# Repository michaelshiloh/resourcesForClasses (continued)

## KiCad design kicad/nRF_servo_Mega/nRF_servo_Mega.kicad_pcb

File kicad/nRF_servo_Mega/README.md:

### nRF_Servo_Mega

[PDF schematic](documentation/nRF_servo_Mega_schematic.pdf)

This shield 
is mean to sit on a Mega (which means using the SPI pins on the ICSP header)
with the Adafruit Music Maker Shield.

Pin usage:

SPI on Mega (used by both Music Maker Shield and nRF radio)
| Arduino Pin |
| --- |
| 51 |
| 52 |
| 53 |

Music Maker Shield

| SPI Signal Name | Description | Arduino Pin |
| --- | --- | --- |
| MCS | VS1053 chip select pin | 7 |
| DCS | VS1053 data select pin | 6 |
| CCS | SD Card chip select pin | 4 |
| DREQ | VS1053 data request interrupt pin | 3 |

#### Revisions

Rev 0.1
- Replace motor numbers with pin numbers
- Improve marking of servo pin assignments
- Add voltage and polarity to screw terminals

#### Revisions
Rev 0.2
- Fix servo motor pin assignments
- Add text indicating servo pin assignment
- Improve visibility of voltage and polarity to screw terminals

#### Suggestions for future
- Extend board past the 36 pin connector and add more servo motor connectors?
- Enlarge text of voltage and polarity to screw terminals

#### Assembly instructions
##### Assembly order
1. .1 ufd cap
1. nRF socket
1. servo pins
1. Stacking headers
1. Screw terminal
1. ICSP header
1. 470 uFD caps

(Note that the order of the instructions and video below are slightly
different - I don't think it makes much of a difference.)

##### Assembly instructions
nRF Servo Mega Shield [video](https://youtu.be/EMkqwKK7xOQ)

1. Install the .1 uFD capacitor in position C1. This is the tiny brown disk
   that says "104" on it. This component is NOT polarized. Solder.
   Cut the excess leads right down to the solder. Discard the cut of portion
   so that it doesn't cause a short circuit
    
2. Cut two pieces of header sockets each with 4 positions. 
    
    They need to be
   held together so use a piece of header pins or the nRF radio module 
   across them to hold them
   together. 

   Solder one pin, and then reheat the pin while you straighten out
   the connector. Solder the rest of the pins.
    
1. Prepare 6 sets of header pins, each with 3 positions. 

    Insert into positions
   D16-D21.
   Solder one pin, straighten, and
   then solder the rest of the pins. You may find it easier to do one header
   at a time instead of trying to do all 6 at once like I did.
    
1. From the bag of feed-through headers, remove six 5 position headers and one
   10 position header. Return the rest to the bag.
    Solder one pin, straighten, then solder the rest. It is very important to
    get these to line up properly so don't solder the rest of the pins until
    the header is straight.
1. Install the feed through header that is two rows of 3 pins. **Note that
   this goes in the opposite direction i.e. the pins face up and the socket
   faces down**. Solder and straighten.
1. Install the two 470 uFD electrolytic capacitors. 
    Note that these components **are polarized** so you have to install them in
    the right direction. The grey stripe must go into the hole with the white
    semicircle.
   Cut the excess leads right down to the solder. Discard the cut of portion
   so that it doesn't cause a short circuit
1. Install the screw terminal. Make sure that the openings face the edge of
   the board. Solder. These pins are quite thick and the hole is quite big, so
   keep feeding solder until the hole fills up.

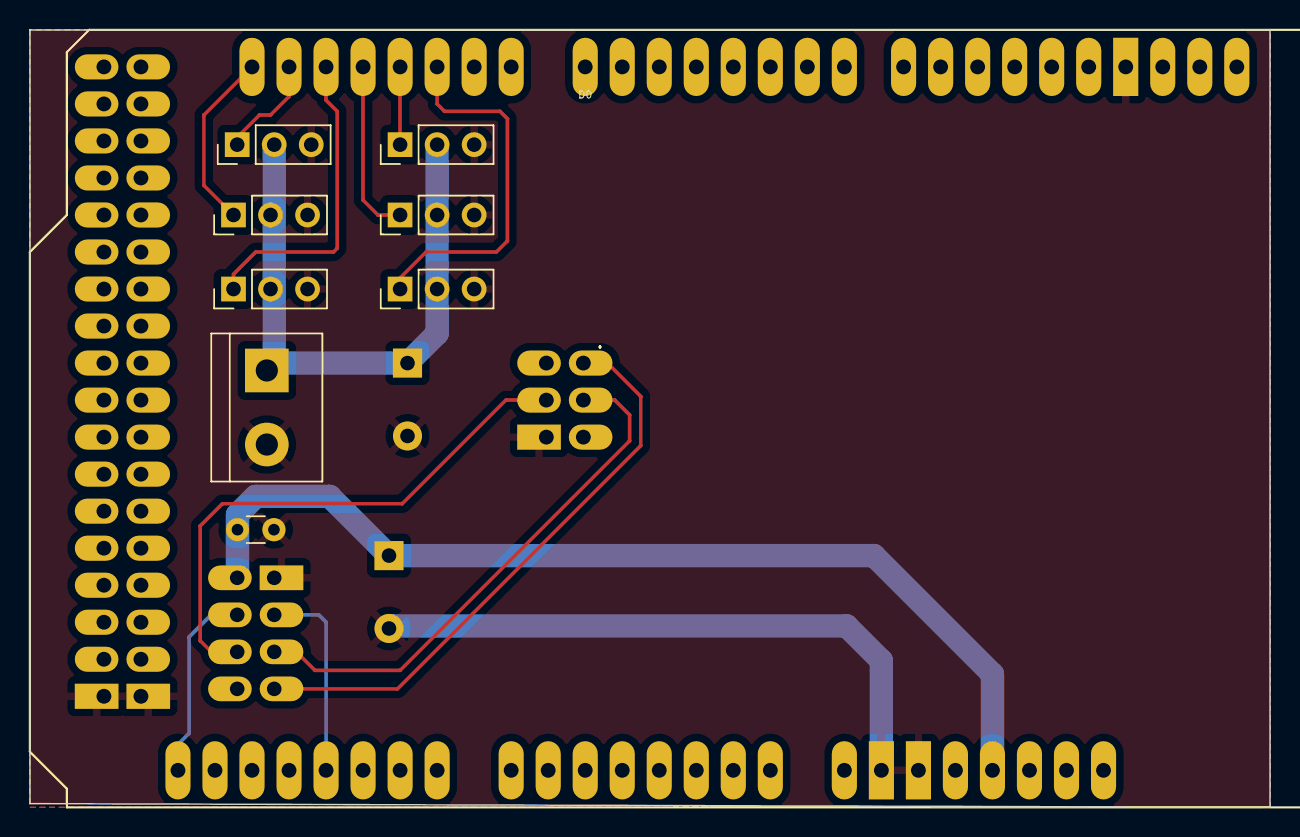
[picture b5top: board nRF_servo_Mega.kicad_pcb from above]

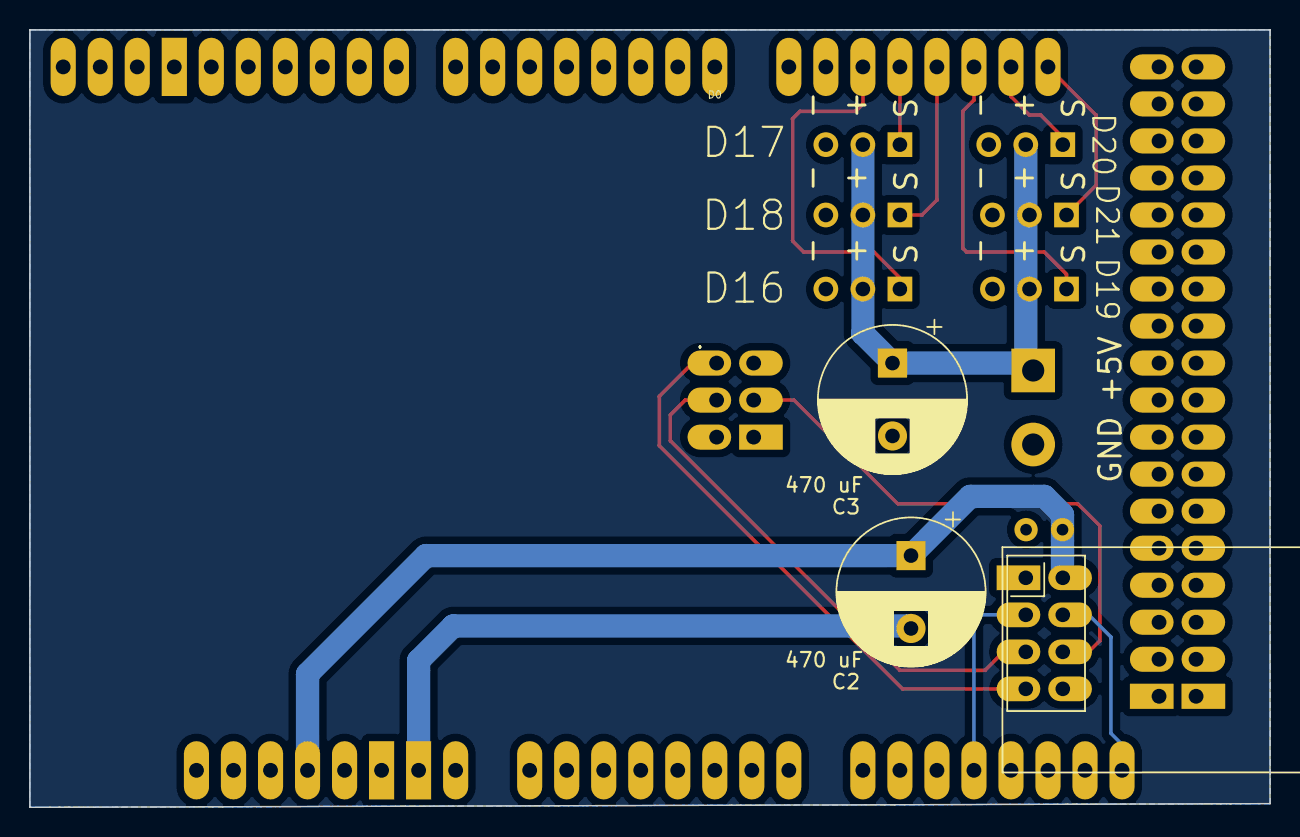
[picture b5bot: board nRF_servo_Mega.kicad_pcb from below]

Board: 2 copper layers, 85.1 x 53.3 mm, 12 parts (4 on the bottom side), 14 nets.

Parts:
C1: .1 uF; C_Disc_D3.0mm_W1.6mm_P2.50mm
C2, C3: 470 uF; CP_Radial_D10.0mm_P5.00mm
D16, D17, D18, D19, D21: Motor_Servo; PinHeader_1x03_P2.54mm_Vertical
J1: Screw_Terminal_01x02; TerminalBlock_bornier-2_P5.08mm
M3: Motor_Servo; PinHeader_1x03_P2.54mm_Vertical
U1: NRF24L01_Breakout; nRF24L01_Breakout
XA1: Arduino_Mega2560_Shield

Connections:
+3.3V: C1.1, C2.1, U1.2 (VCC), XA1.3V3 (3.3V)
GND: C1.2, C2.2, C3.2, D16.3 (-), D17.3 (-), D18.3 (-), D19.3 (-), D21.3 (-), J1.2, M3.3 (-), U1.1 (GND), XA1.GND1 (GND), XA1.GND2 (GND), XA1.GND3 (GND), XA1.GND4 (SPI_GND), XA1.GND5 (GND), XA1.GND6 (GND)
unnamed: C3.1, D16.2 (+), D17.2 (+), D18.2 (+), D19.2 (+), D21.2 (+), J1.1, M3.2 (+)
unnamed: D19.1 (PWM), XA1.D19 (D19/RX1)
unnamed: D21.1 (PWM), XA1.D21 (D21/SCL)
unnamed: M3.1 (PWM), XA1.D20 (D20/SDA)
unnamed: D16.1 (PWM), XA1.D16 (D16/TX2)
unnamed: D18.1 (PWM), XA1.D18 (D18/TX1)
unnamed: D17.1 (PWM), XA1.D17 (D17/RX2)
unnamed: U1.3 (CE), XA1.A11
unnamed: U1.7 (MISO), XA1.MISO (SPI_MISO)
unnamed: U1.6 (MOSI), XA1.MOSI (SPI_MOSI)
unnamed: U1.5 (SCK), XA1.SCK (SPI_SCK)
unnamed: U1.4 (~CSN), XA1.A15

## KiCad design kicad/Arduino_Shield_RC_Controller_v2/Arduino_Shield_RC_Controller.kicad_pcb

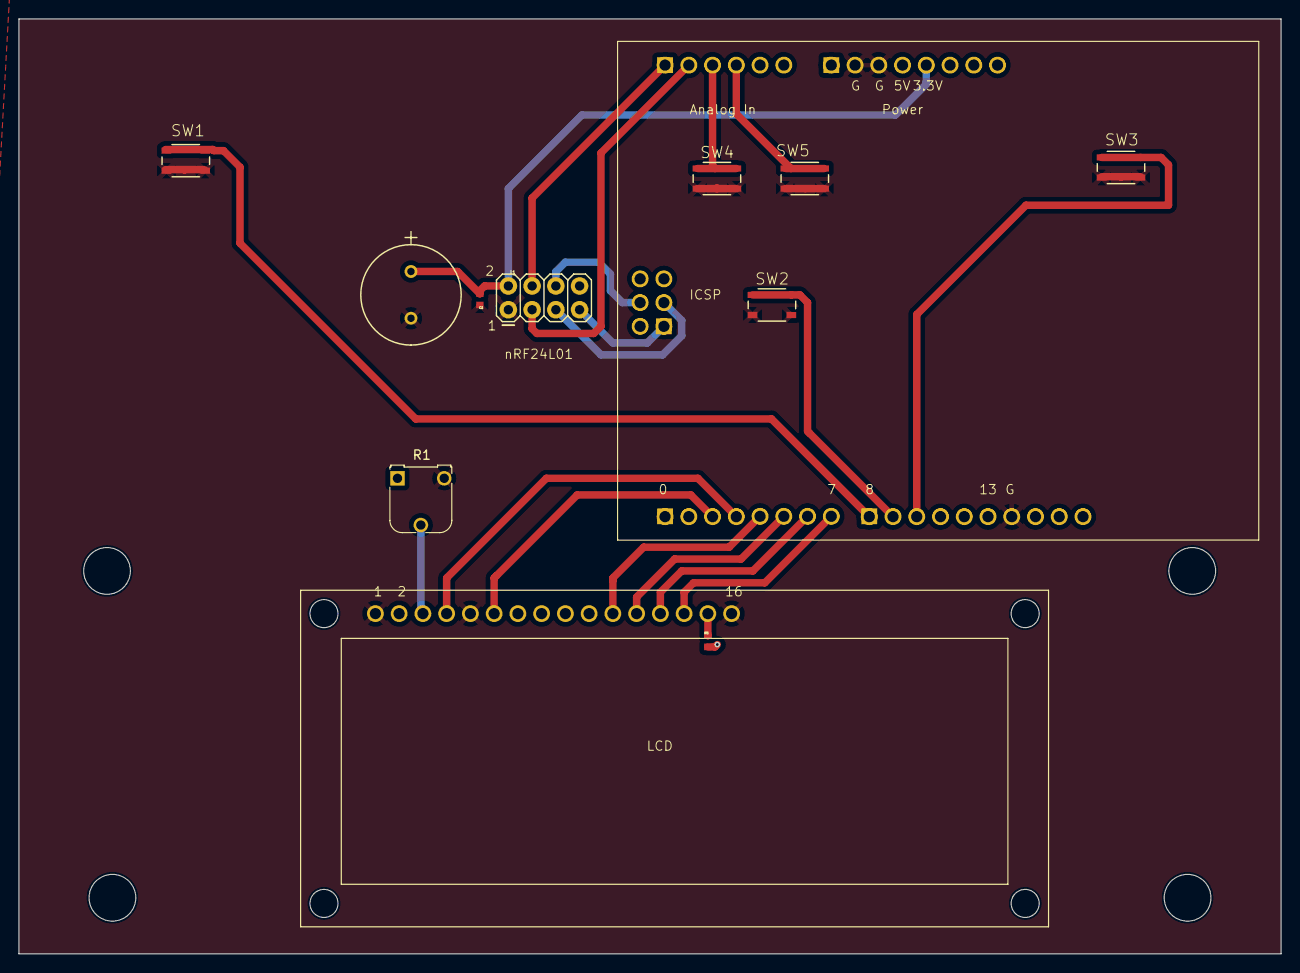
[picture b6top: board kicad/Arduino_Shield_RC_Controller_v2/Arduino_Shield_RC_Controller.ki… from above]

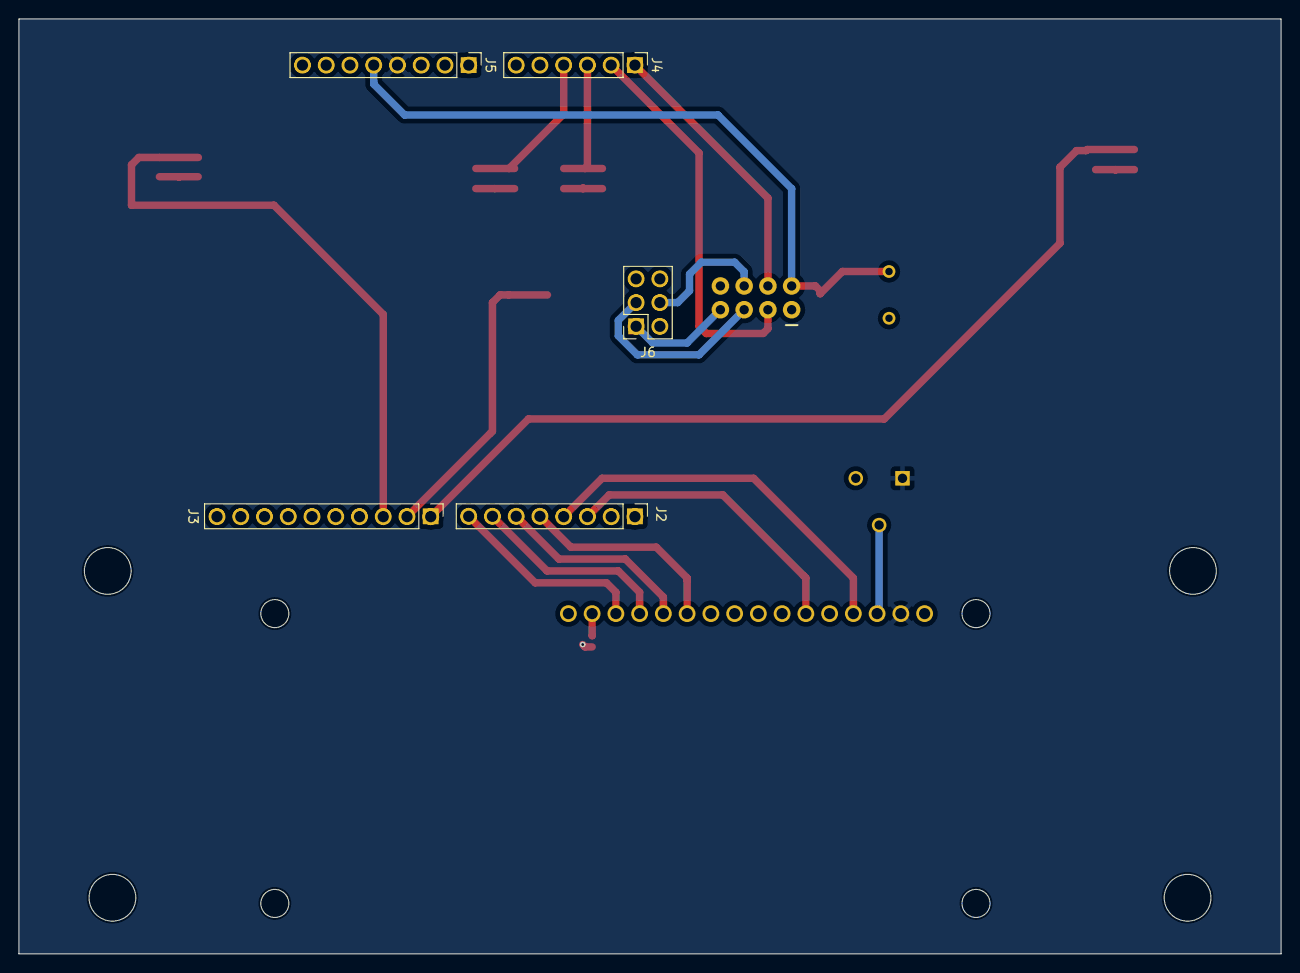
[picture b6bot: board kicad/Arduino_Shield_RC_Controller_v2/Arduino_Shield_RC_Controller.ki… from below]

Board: 2 copper layers, 135.0 x 100.0 mm, 21 parts (5 on the bottom side), 26 nets.

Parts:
@HOLE0, @HOLE1, @HOLE2, @HOLE3: (no value)
AR1: ARDUINO_R3
C1: 0.1uF; 0402
C2: CAP_470UF_RAD_TH; CAP_YX_10X16_RUB
J1: CONN_04X2; 2X4
J2, J5: Conn_01x08_Pin; PinHeader_1x08_P2.54mm_Vertical
J3: Conn_01x10_Pin; PinHeader_1x10_P2.54mm_Vertical
J4: Conn_01x06_Pin; PinHeader_1x06_P2.54mm_Vertical
J6: Conn_02x03_Odd_Even; PinSocket_2x03_P2.54mm_Vertical
LCD1: ADM1602K
R1: R-TRIMM3103; Potentiometer_Runtron_RM-065_Vertical
R5: 470R0; 0402
SW1, SW2, SW3, SW4, SW5: PTS810SJG250SMTRLFS; PTS810

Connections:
+3.3V: AR1.P35 (3.3V), C1.P$2 (2), C2.1, J1.2, J5.5
+5V: AR1.P34 (5V), J5.4, LCD1.P2 (VDD5), R1.1 (A), R5.P$2 (2)
/MISO: AR1.P19 (CIPO/PB4), J1.7, J6.1
/MOSI: AR1.P22 (COPI/PB3), J1.6, J6.4
/V0: LCD1.P3 (V0), R1.2 (S)
GND: AR1.P4 (GND0), AR1.P32 (GND1), AR1.P33 (GND2), C1.P$1 (1), C2.2, J1.1, J3.7, J5.2, J5.3, LCD1.P1 (VSS-GND), LCD1.P5 (R/W), LCD1.P16 (K), R1.3 (E), SW1.3, SW1.4, SW2.3, SW2.4, SW3.3, SW3.4, SW4.3, SW4.4, SW5.3, SW5.4
unnamed: AR1.P16 (2), J2.3, LCD1.P6 (E)
unnamed: AR1.P15 (3), J2.4, LCD1.P4 (RS)
unnamed: AR1.P14 (4), J2.5, LCD1.P11 (DB4)
unnamed: AR1.P13 (5), J2.6, LCD1.P12 (DB5)
unnamed: AR1.P12 (6), J2.7, LCD1.P13 (DB6)
unnamed: AR1.P11 (7), J2.8, LCD1.P14 (DB7)
unnamed: AR1.P10 (8), J3.1, SW1.1, SW1.2
unnamed: AR1.P9 (9), J3.2, SW2.1, SW2.2
unnamed: AR1.P8 (10), J3.3, SW3.1, SW3.2
unnamed: AR1.P30 (A0), J4.6
unnamed: AR1.P29 (A1), J4.5
unnamed: AR1.P28 (A2), J4.4, SW5.1, SW5.2
unnamed: AR1.P27 (A3), J4.3, SW4.1, SW4.2
unnamed: AR1.P26 (A4), J1.3, J4.2
unnamed: AR1.P25 (A5), J1.4, J4.1
unnamed: AR1.P24 (GND3), J6.6
unnamed: AR1.P23 (RESET2), J6.5
unnamed: AR1.P21 (SCK/PB5), J1.5, J6.3
unnamed: AR1.P20 (VDD5), J6.2
unnamed: LCD1.P15 (A), R5.P$1 (1)

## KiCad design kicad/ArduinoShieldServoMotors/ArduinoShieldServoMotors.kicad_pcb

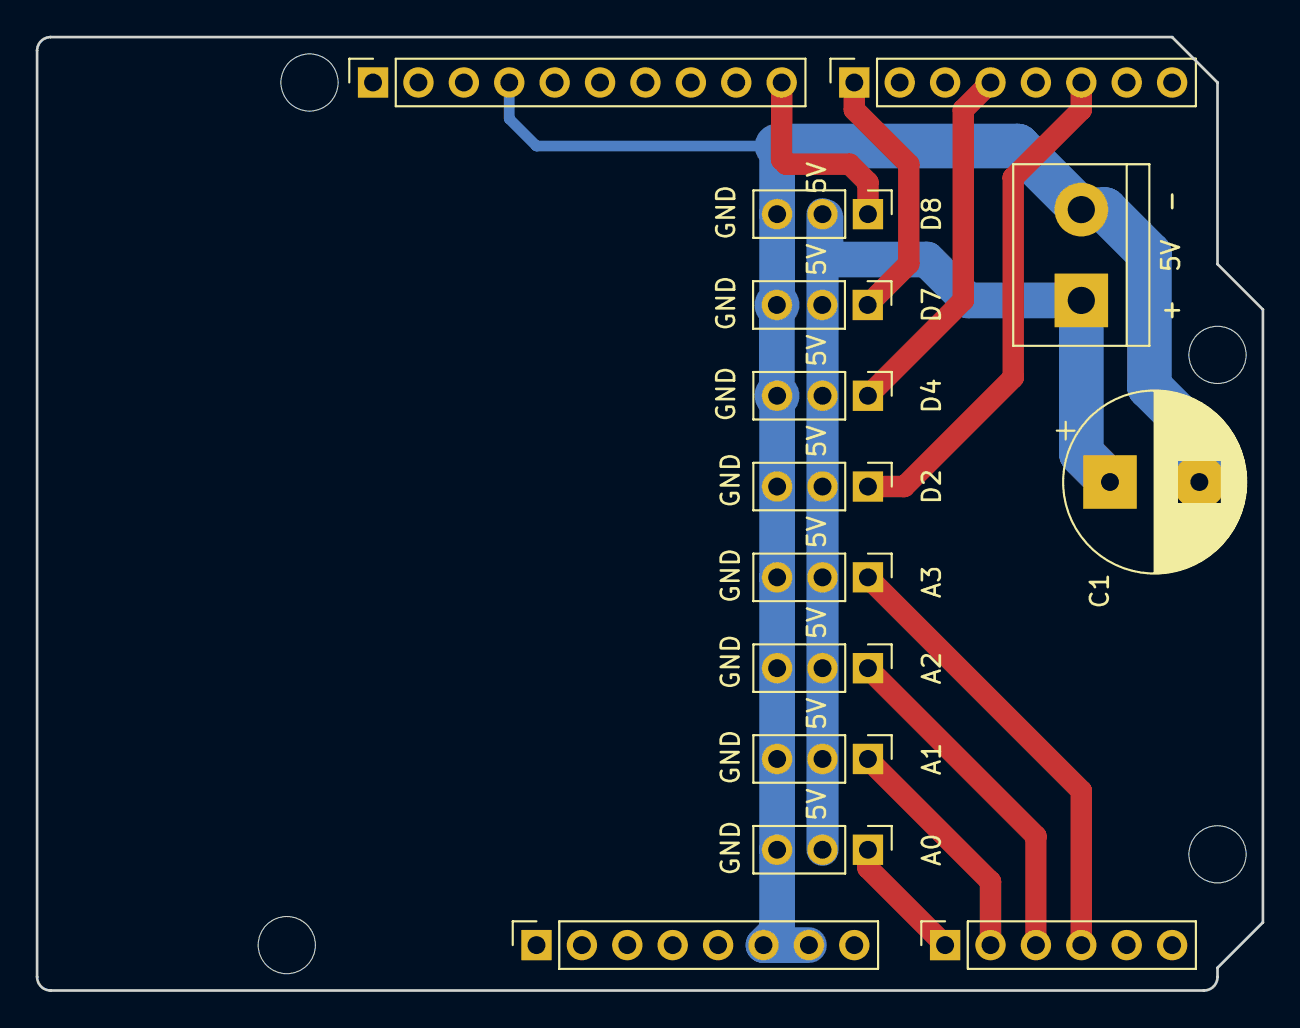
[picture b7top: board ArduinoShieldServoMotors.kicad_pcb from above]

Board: 2 copper layers, 68.6 x 53.3 mm, 18 parts (0 on the bottom side), 13 nets.

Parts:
+__5V__-1: Screw_Terminal_01x02; TerminalBlock_bornier-2_P5.08mm
A0, A1, A2, A3: Conn_01x03; PinHeader_1x03_P2.54mm_Vertical
C1: 470 ufd; CP_Radial_D10.0mm_P5.00mm
D2, D4, D7, D8: Conn_01x03; PinHeader_1x03_P2.54mm_Vertical
J1: Power; PinSocket_1x08_P2.54mm_Vertical
J2: Digital/PWM; PinSocket_1x10_P2.54mm_Vertical
J3: Analog; PinSocket_1x06_P2.54mm_Vertical
J4: Digital/PWM; PinSocket_1x08_P2.54mm_Vertical
MH1, MH2, MH3, MH4: MountingHole_3.2mm

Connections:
/2: D2.1, J4.6
/4: D4.1, J4.4
/7: D7.1, J4.1
/8: D8.1, J2.10
/A0: A0.1, J3.1
/A1: A1.1, J3.2
/A2: A2.1, J3.3
/A3: A3.1, J3.4
/AREF: J1.1, J2.3
/SCL/A5: J2.1, J3.6
/SDA/A4: J2.2, J3.5
GND: +__5V__-1.2, A0.3, A1.3, A2.3, A3.3, C1.2, D2.3, D4.3, D7.3, D8.3, J1.6, J1.7, J2.4
unnamed: +__5V__-1.1, A0.2, A1.2, A2.2, A3.2, C1.1, D2.2, D4.2, D7.2, D8.2

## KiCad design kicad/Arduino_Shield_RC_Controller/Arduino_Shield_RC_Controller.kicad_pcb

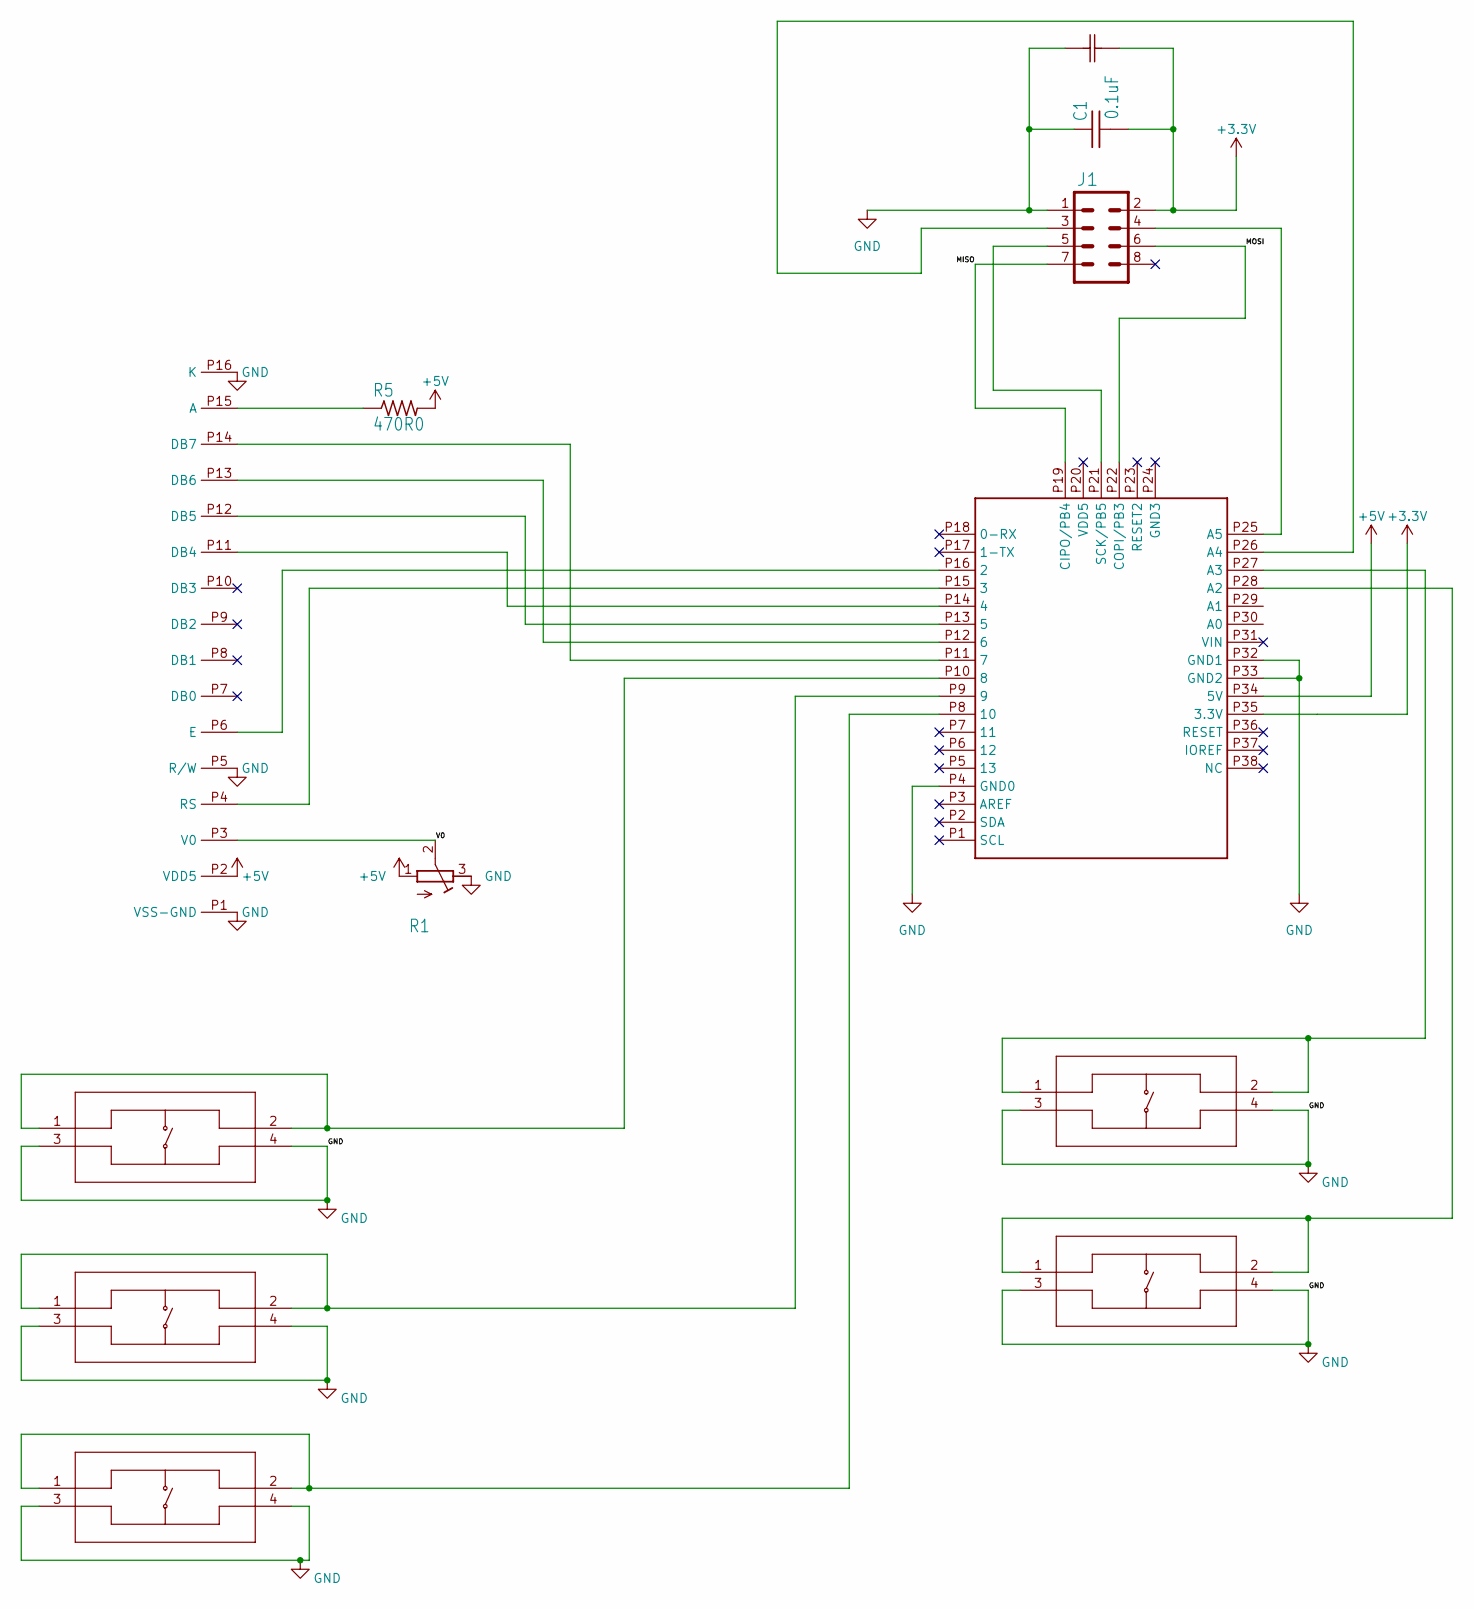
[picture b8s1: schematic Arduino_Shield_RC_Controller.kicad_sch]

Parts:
AR1: ARDUINO_R3
C1: 0.1uF; 0402
C2: CAP_470UF_RAD_TH; CAP_YX_10X16_RUB
J1: CONN_04X2; 2X4
LCD1: ADM1602K
R1: R-TRIMM3103; RTRIM3103
R5: 470R0; 0402
SW1, SW2, SW3, SW4, SW5: PTS810SJG250SMTRLFS; PTS810

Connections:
+3.3V: AR1.P35 (3.3V), C1.P$2 (2), C2.1, J1.2
+5V: AR1.P34 (5V), LCD1.P2 (VDD5), R1.1 (A), R5.P$2 (2)
/MISO: AR1.P19 (CIPO/PB4), J1.7
/MOSI: AR1.P22 (COPI/PB3), J1.6
/V0: LCD1.P3 (V0), R1.2 (S)
GND: AR1.P4 (GND0), AR1.P32 (GND1), AR1.P33 (GND2), C1.P$1 (1), C2.2, J1.1, LCD1.P1 (VSS-GND), LCD1.P5 (R/W), LCD1.P16 (K), R1.3 (E), SW1.3, SW1.4, SW2.3, SW2.4, SW3.3, SW3.4, SW4.3, SW4.4, SW5.3, SW5.4
unnamed: AR1.P16 (2), LCD1.P6 (E)
unnamed: AR1.P15 (3), LCD1.P4 (RS)
unnamed: AR1.P14 (4), LCD1.P11 (DB4)
unnamed: AR1.P13 (5), LCD1.P12 (DB5)
unnamed: AR1.P12 (6), LCD1.P13 (DB6)
unnamed: AR1.P11 (7), LCD1.P14 (DB7)
unnamed: AR1.P10 (8), SW1.1, SW1.2
unnamed: AR1.P9 (9), SW2.1, SW2.2
unnamed: AR1.P8 (10), SW3.1, SW3.2
unnamed: AR1.P28 (A2), SW5.1, SW5.2
unnamed: AR1.P27 (A3), SW4.1, SW4.2
unnamed: AR1.P26 (A4), J1.3
unnamed: AR1.P25 (A5), J1.4
unnamed: AR1.P21 (SCK/PB5), J1.5
unnamed: LCD1.P15 (A), R5.P$1 (1)

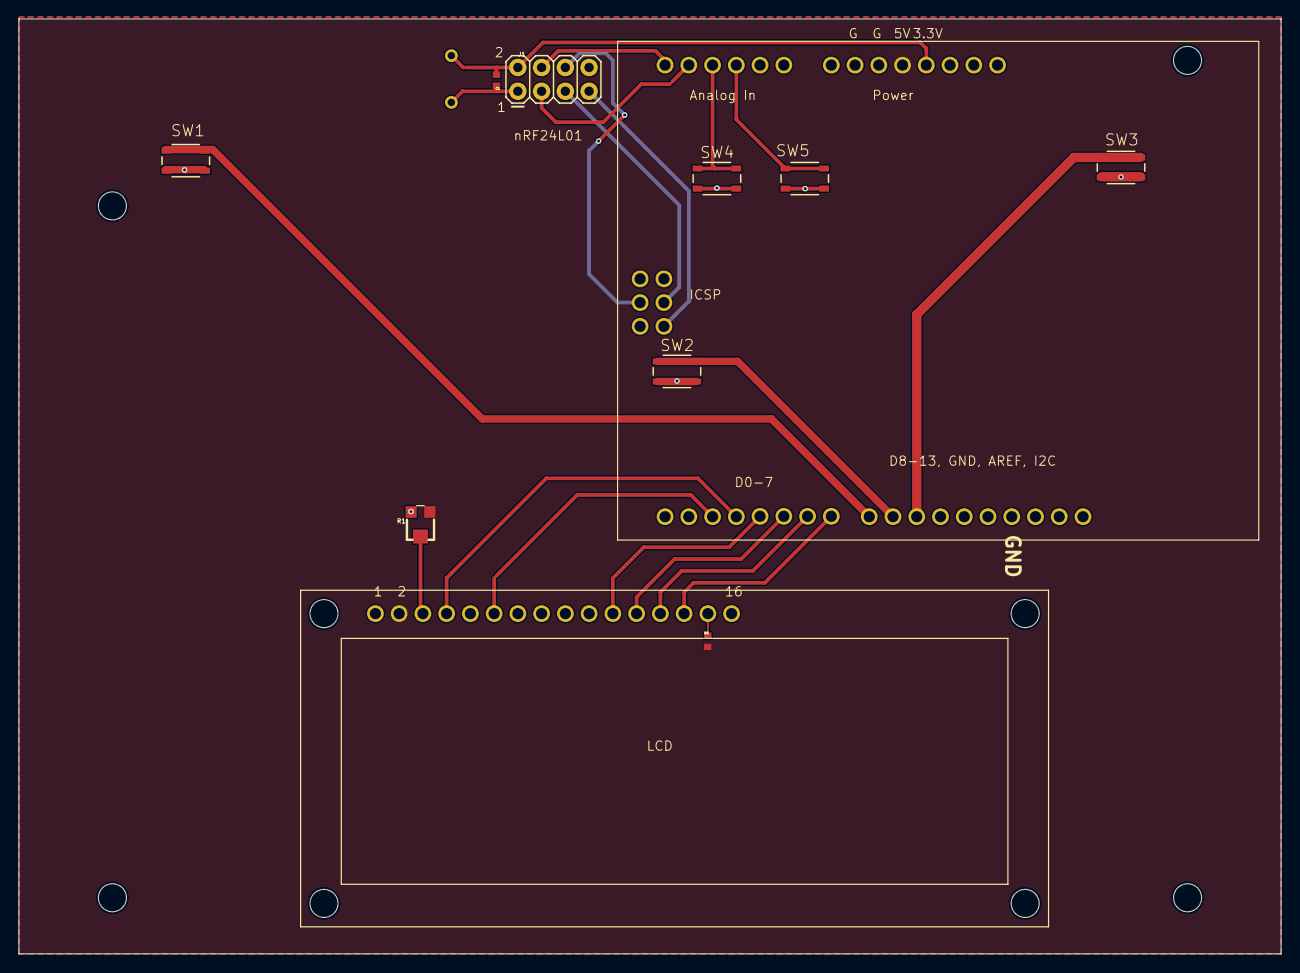
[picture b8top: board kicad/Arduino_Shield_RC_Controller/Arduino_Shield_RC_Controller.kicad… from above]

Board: 2 copper layers, 135.0 x 100.0 mm, 16 parts (1 on the bottom side), 21 nets.

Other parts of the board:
@HOLE0, @HOLE1, @HOLE2, @HOLE3: (no value)

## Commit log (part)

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2019-02-19 bidirectional!
2019-02-21 added blinkUsingUDPEchoServer
2019-02-21 added node programs
2019-03-04 server both http and tcp
2019-03-04 added node server
2019-03-04 added arduino sketch
2019-03-06 trying to get socket to work
2019-03-07 arduino udp device, initial entry
2019-03-07 using websocket to communicate back to the server
2019-03-07 initial entry server.js
2019-03-07 more pieces in place
2019-03-07 now arduino receives udp message from server
2019-03-12 changed function syntax to the modern style using => instead of the word function
2019-03-12 implemented web page button to turn on LED on Arduino
2019-03-12 resolved conflicts in class
2019-03-14 added slider
2019-03-14 added a second slider
2019-03-15 removed tcpAndHttpServer since it is not working
2019-03-15 changes to arduino code to allow binary messages between arduino and server
2019-03-16 display an image when button is clicked
2019-04-25 testing gpio access
2019-04-25 blink only when client connects
2019-04-25 turn on LED on connection time is not working yet
2019-04-25 added time check not reported to web page yet
2019-04-25 added link to time comparison which i have not yet implemented
2019-04-26 a little crude but all functionality implemented
2019-04-26 set time to proper time
2019-05-02 renamed to receiver
2019-08-29 fixed numbers
2019-09-05 added motor shield
2019-09-05 removed unnecessary tutorial
2019-10-25 added github cheatsheet
2019-10-30 added Processing resource
2019-10-30 fixed link to example
2019-10-30 added shiffman video object tutorial
2019-11-21 dan shiffman videos
2019-12-13 Where is the Upload Files button
2019-12-13 link to upload file button image
2020-02-13 added analogReadingAndWriting
2020-02-15 more readings
2020-02-18 frank lloyd wrights article
2020-02-24 renamed automata books properly
2020-02-24 fixed name
2020-02-26 new book
2020-03-15 started
2020-03-20 fusion resources
2020-04-12 added cabaret mechanical movements
2020-04-12 added link to intro to mechanisms course at cmu
2020-04-12 added hackaday mechanism series
2020-04-29 added critical making and open source
2020-05-03 added processing sketches
2020-05-30 added some git command lines
2020-06-16 moved from elsewhere
2020-06-21 added thanks to adafruit
2020-09-08 added a resource
2020-09-14 organized blink wout delay
2020-11-24 added some FSM resources
2020-11-28 added arduino smoothing
2020-11-28 added notes to smoothing resources
2021-01-15 added textbooks for Robota Psyche
2021-01-16 added weizenbaum
2021-01-19 added license
2021-01-23 added panel joinery ideas
2021-02-03 added link to bobcat
2021-02-15 first step in flocking, based on Shiffmans The Nature of Code
2021-02-20 initial entry for evolution
2021-02-21 initial stage of evolution implemented with DNA and vehicles dying for lack of energy
2021-02-22 added dna
2021-02-24 added debugging and inspecting
2021-03-24 added the five robots a taxonomy for roboethics
2021-03-30 added first two chapters of I Robot
2021-03-31 added full book I Robot
2021-04-03 added projectsions
2021-04-04 initial steps at association
2021-04-07 added hook for association
2021-04-08 basic serial bidirectional handshaking example
2021-04-09 returned to default running mode
2021-05-20 trivial MQTT example
2021-06-24 added solution to a class exercise
2021-06-24 added explanation why sending 0 in setup()
2021-06-24 added flashing LED to a bouncing ball
2021-06-24 added handshaking
2021-07-04 grouped all examples that show how to avoid using delay
2021-07-04 starting new example
2021-07-04 state machine example
2021-07-05 set melodyPlayer pin as in Flasher
2021-07-06 first in a series of state machines
2021-09-23 example of data visualization
2021-09-25 nRF24L01 examples
2021-09-25 moved to subdirectory
2021-09-26 added schematic
2021-09-27 added frame differencing example
2021-09-29 added pin numbers
2021-09-29 changed switch pin
2021-10-02 added Thais resources
2021-10-05 switched to binary numbers
2021-10-06 examples for sending two bytes using the nRF24L01 radio modules
2021-10-06 explained difference between the examples
2021-10-10 added debugging
2021-10-21 added processing cheat sheet
2021-11-06 upload difficulties suggestions
2021-11-13 simplified
2021-11-24 moved book to the right directory
2021-11-24 do not use pdf
2021-11-25 reverted back to working version; for some reason I had the transmitter code
2022-01-25 converted my simpleProcessingClassExample to p5.js
2022-01-25 typo
2022-01-25 removed smooth() because it is active by default
2022-01-29 added more material
2022-01-29 more
2022-02-01 added Vehicles
2022-02-07 added Table_of_Mechanicks_Cyclopaedia_Volume_2.jpg
2022-02-18 added The Machine Question
2022-02-18 added Joanna Bryson
2022-02-23 better structure for code
2022-02-23 removed invalid function call
2022-03-23 added Affective Computers
2022-03-24 added the word connection to the arduino upload debugging
2022-03-24 specified arduino connection problems
2022-04-26 added picture showing how to put radio module on breadboard
2022-04-27 separated dmm section
2022-05-01 minimal example decoding two channels of hobby RC using the two hardware interrupt pins
2022-05-02 decoding hobby RC with Arduino pin change interrupts
2022-05-07 added git for windows resources
2022-05-24 changed variable for pin names to be more descriptive
2022-06-09 added a book
2022-07-08 new article
2022-09-07 added more resources
2022-09-16 added link to close up video pin soldering
2022-09-17 added creativity resource
2022-09-19 added pwm failsafe reading
2022-10-10 added new nRF example with two LEDs and two switches
2022-10-10 added comment about which library is required
2022-10-12 how to ask for help resources
2022-10-15 added michael candy
2022-10-24 Update rf24TwoSwitchesTwoLEDs.ino
    transmitter needs to check both switches and receiver needs to use decimal numbers in switch statement
2022-10-24 Update rf24TwoSwitchesTwoLEDs.ino
    corrected spelling of TMRh20
2022-10-24 Update rf24TwoSwitchesTwoLEDs.ino
    receiver needs to open pipe for reading and to start listening
2022-11-14 added reference to the proper library to all examples
2022-11-16 debugging rf24TwoSwitchesTwoLEDs.ino
2022-11-20 check for messages more frequently than sending
2022-11-20 added resource regarding nRF addresses
2022-11-20 fixed a million bugs
2022-11-22 more experiments with nRF radios
2022-11-23 rf24ControlPanelPerformingRobotsNoHandshaking basic functionality works
2022-11-23 control panel makes music maker shield play clips
2022-11-23 added servo motors but not tested yet
2022-11-24 fixed typo in xmtr and running test to abuse servo
2022-11-25 getting ready to testing different channels and power levels
2022-11-25 different channels and addresses work
2022-11-26 if RF24.write fails print details
2022-11-27 fixed typo
2022-11-27 counting transmit failures
2022-11-27 less printing so easier to see what is going on
2022-12-01 typo in abuseServos()
2022-12-02 renamed rf24ControlPanelPerformingRobotsNoHandshaking to rf24MoreReliable
2022-12-02 created template based on work to increase reliability
2022-12-02 allocated channels and addresses for students
2022-12-10 removed printf library to try to save some space
2022-12-10 modified selector bits for the control panel
2022-12-11 put strings in flash memory
2023-01-11 added some robotic resources
2023-01-25 added many mechatronics references for Machine Lab spring 2023
2023-01-25 fixed some links
2023-01-31 added cam example
2023-02-20 added wire wrapping machine
2023-02-24 added some clocks
2023-03-14 added article about ai generated art featuring merritt mooore
2023-03-28 walking boots
2023-04-12 reverted to last known good performing robot template
2023-05-08 added photo of large servo asme-04 configured in servo mode
2023-05-08 starting a bidirectional example
2023-05-08 first draft of bidirectional code, completely untested
2023-05-17 added de re metallica
2023-06-09 added animatronic resource
2023-09-10 moved nRF control panel to here
2023-09-10 added bill of materials
2023-09-10 roughed out schematic for nRFControlPanel. Have not finished assigning pins to allow flexible layout.
2023-09-25 comments to minimalMoreChannels
2023-09-29 added kicad_prl to .gitignore
2023-09-29 added design rule file .kicad_dru
2023-09-30 finished layout added a couple extra buttons
2023-10-11 created new template for RF24 Performing Robots
2023-10-13 added README.md
2023-10-13 nrf mega shield that works with music maker shield
2023-10-13 added kicad sym-lib-table
2023-10-28 neo matrix using graphics library works but not servo or sound yet
2023-10-28 neo matrix using graphics library and music maker shield work but not servo yet
2023-10-28 neo matrix using graphics library and music maker shield and servo all work
2023-11-19 added channel assignments Performing Robots Fall 2023
2023-11-20 Fixed gibberish error
2023-11-22 acknowledged akhats bug fix
2023-11-22 display custom address byte and channel number
2023-12-25 a small board to make it easier to connect to an L298 module
2024-01-27 added links to machine tool movies
2024-01-28 added datasheets for giant servo
2024-01-28 reorganized
2024-03-24 arduino shield servo uno
2024-03-24 sent off ArduinoShieldServoMotors to JLCPCB
2024-04-03 fade NeoPixels without using the delay function
2024-04-05 added warning that many NeoPixels may introduce delays
2024-04-05 added manyServosNoDelay
2024-04-07 added mounting plates for l298 and giant servo
2024-07-06 added Forrest Mims notebook
2024-08-03 version 2 of performing robots controller
2024-09-07 starting the Hobby RC and Motor Control shield
2024-09-08 added component footprints .kicad_mod files
2024-09-16 added the kicad_dru file to git, not sure its necessary
2024-11-06 added manual for the RC4GS hobby radio system
2024-11-10 added pan tilt resources
2024-11-12 new template for 2024
2024-11-12 updated rc control panel for fall 2024
2024-11-12 corrected link to the receiver design files
2024-11-12 corrected pin definitions for servo motor connectors
2025-02-15 motor matrix adapter
2025-08-06 added New Media Art
2025-08-07 added show catalog for Cybernetic Serendipitiy
2025-08-07 moved books to doc
2025-08-12 added paragraphs on conceptual art
2025-08-12 moma catalog
2025-08-12 another chapter
2025-09-13 added DesignCyberneticsNavigatingTheNew.pdf and Table_of_Mechanicks_Cyclopaedia_Volume_2.jpg
2025-09-20 rev 2 of arduino shield hobby rc and motor control
2025-09-20 added link to Eduardo Kac ORIGIN AND DEVELOPMENT OF ROBOTIC ART
2025-09-20 moved srl clip to doc
2025-09-20 srl doom clip
2025-09-24 example of bad solder joint
2025-09-26 changed the pin numbers to correspond to the Arduino Shield Hobby RC Motor Control
2025-09-28 machine art in the twentieth century
2025-09-30 added information arts
2025-10-16 added servo pinouts to silkscreen
2025-10-19 giant servo resources
2025-10-22 image hints
2025-10-29 added description of rev 0.2 and assembly order
2025-10-29 added assembly instructions
2025-10-31 changed channel and address assignments for fall 2025
2025-11-01 added pictures of assembling nRF
2025-11-01 added some pictures of nRF assembly
2025-11-01 added APC PCB
2025-11-01 changed nrf pin numbers to be correct for receiver
2025-11-01 receiver prints out channel and address, like the transmitter does
2025-11-01 added comment about radio.write retval
2025-11-02 changed default to receeiver
2025-11-15 added hobbyRCAndMotorController which combines hobbyRC and motor controller
2025-11-15 according to printed messages code is working. Next test with motor controller
2025-11-16 fixed bug in minimalMoreChannels: space not allocated for six channels, but six channels read
2025-11-16 added motor control to the hobbyRC examples
2025-11-16 test nRF pins are correct depending on rcvr or xmtr; example showing how to move servo motor gradually
2025-11-29 realized that I should save sym-lib-table
2025-12-21 new shield for a great many servo motors
2026-01-04 added links to further information and help with debugging
2026-01-04 another nRF resource
2026-01-07 improved layout
2026-01-08 added art criticism section
2026-01-08 added artist statement section
2026-01-10 minor changes for Machine Lab 2026
2026-01-23 soldering
2026-01-23 debugging
2026-03-05 fixed broken link
2026-03-09 more books
2026-04-06 added soldering resource
2026-04-15 added resources
2026-04-16 added kathleens wearables website
2026-05-02 added servo resources
